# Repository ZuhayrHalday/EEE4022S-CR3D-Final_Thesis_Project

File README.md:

# Cosmic Ray Detector and Data Dispatcher (CR3D)
### Undergraduate Thesis Project – EEE4022S 2025  
**Author:** Zuhayr Halday
**Supervisor:** Prof Simon Winberg  
**Institution:** Department of Electrical and Electronic Engineering, University of Cape Town  
**Year:** 2025  

---

## 📖 Project Overview
The **Cosmic Ray Detector and Data Dispatcher (CR3D)** is a compact, educationally oriented **muon detection framework** designed as part of an undergraduate thesis project.  
The system integrates **physics-based simulation**, **analog front-end (AFE) design**, and **modular data acquisition software** to demonstrate a full cosmic-ray detection pipeline — from **muon energy deposition** to **digitized data logging**.

Due to constraints in component availability and time, the detector was developed using a **simulation-centered methodology** that validated all major subsystems analytically and experimentally through proxy testing.

---

## 🧩 System Architecture
CR3D comprises **three interdependent subsystems** reflected in the repo structure:

1. **Scintillator Simulation Subsystem**  
   - Implemented using **Geant4** to model muon interactions with an EJ-200 scintillator.  
   - Produces photon count and timing histograms for varied muon energies, path lengths, and quenching parameters.  
   - Output: `photon_counts.csv` and `time_histograms.csv`

2. **Analog Front-End (AFE) Subsystem**  
   - Designed and simulated in **LTSpice** with analytical modeling in MATLAB.  
   - Includes a **transimpedance amplifier (TIA)**, **peak-hold detector**, and **RC low-pass filter**.  
   - Hardware prototype verified using **controlled current injection** tests.

3. **Firmware and Data Logging Subsystem**  
   - Arduino Nano firmware (C++) for analog sampling, event detection, and serial data transmission.  
   - Python GUI (`cr3d_logger.py`) built with **Tkinter** and **Matplotlib** for real-time plotting, environmental annotation, and structured CSV logging.

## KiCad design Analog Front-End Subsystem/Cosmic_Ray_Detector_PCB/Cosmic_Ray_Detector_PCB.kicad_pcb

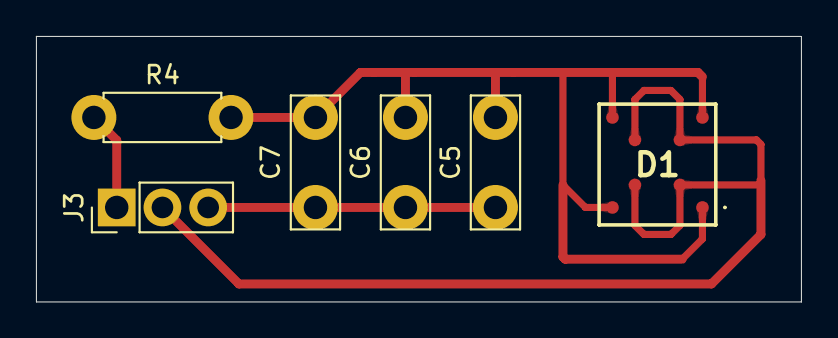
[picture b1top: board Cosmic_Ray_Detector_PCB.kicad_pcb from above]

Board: 2 copper layers, 42.5 x 14.8 mm, 6 parts (0 on the bottom side), 4 nets.

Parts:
C5: 1nF; C_Rect_L7.2mm_W2.5mm_P5.00mm_FKS2_FKP2_MKS2_MKP2
C6: 10nF; C_Rect_L7.2mm_W2.5mm_P5.00mm_FKS2_FKP2_MKS2_MKP2
C7: 100nF; C_Rect_L7.2mm_W2.5mm_P5.00mm_FKS2_FKP2_MKS2_MKP2
D1: AFBR-S4N66P014M; AFBRS4N66P014M
J3: 3 Pin Male; PinHeader_1x03_P2.54mm_Vertical
R4: 68; R_Axial_DIN0207_L6.3mm_D2.5mm_P7.62mm_Horizontal

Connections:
GND: C5.1, C6.1, C7.1, J3.3
unnamed: D1.2 (ANODE_3), J3.2
unnamed: C5.2, C6.2, C7.2, D1.1 (CATHODE_1), R4.2
unnamed: J3.1, R4.1

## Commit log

2025-10-28 Fixed Code Commenting
2025-10-28 Added README
2025-10-28 Added final thesis report
